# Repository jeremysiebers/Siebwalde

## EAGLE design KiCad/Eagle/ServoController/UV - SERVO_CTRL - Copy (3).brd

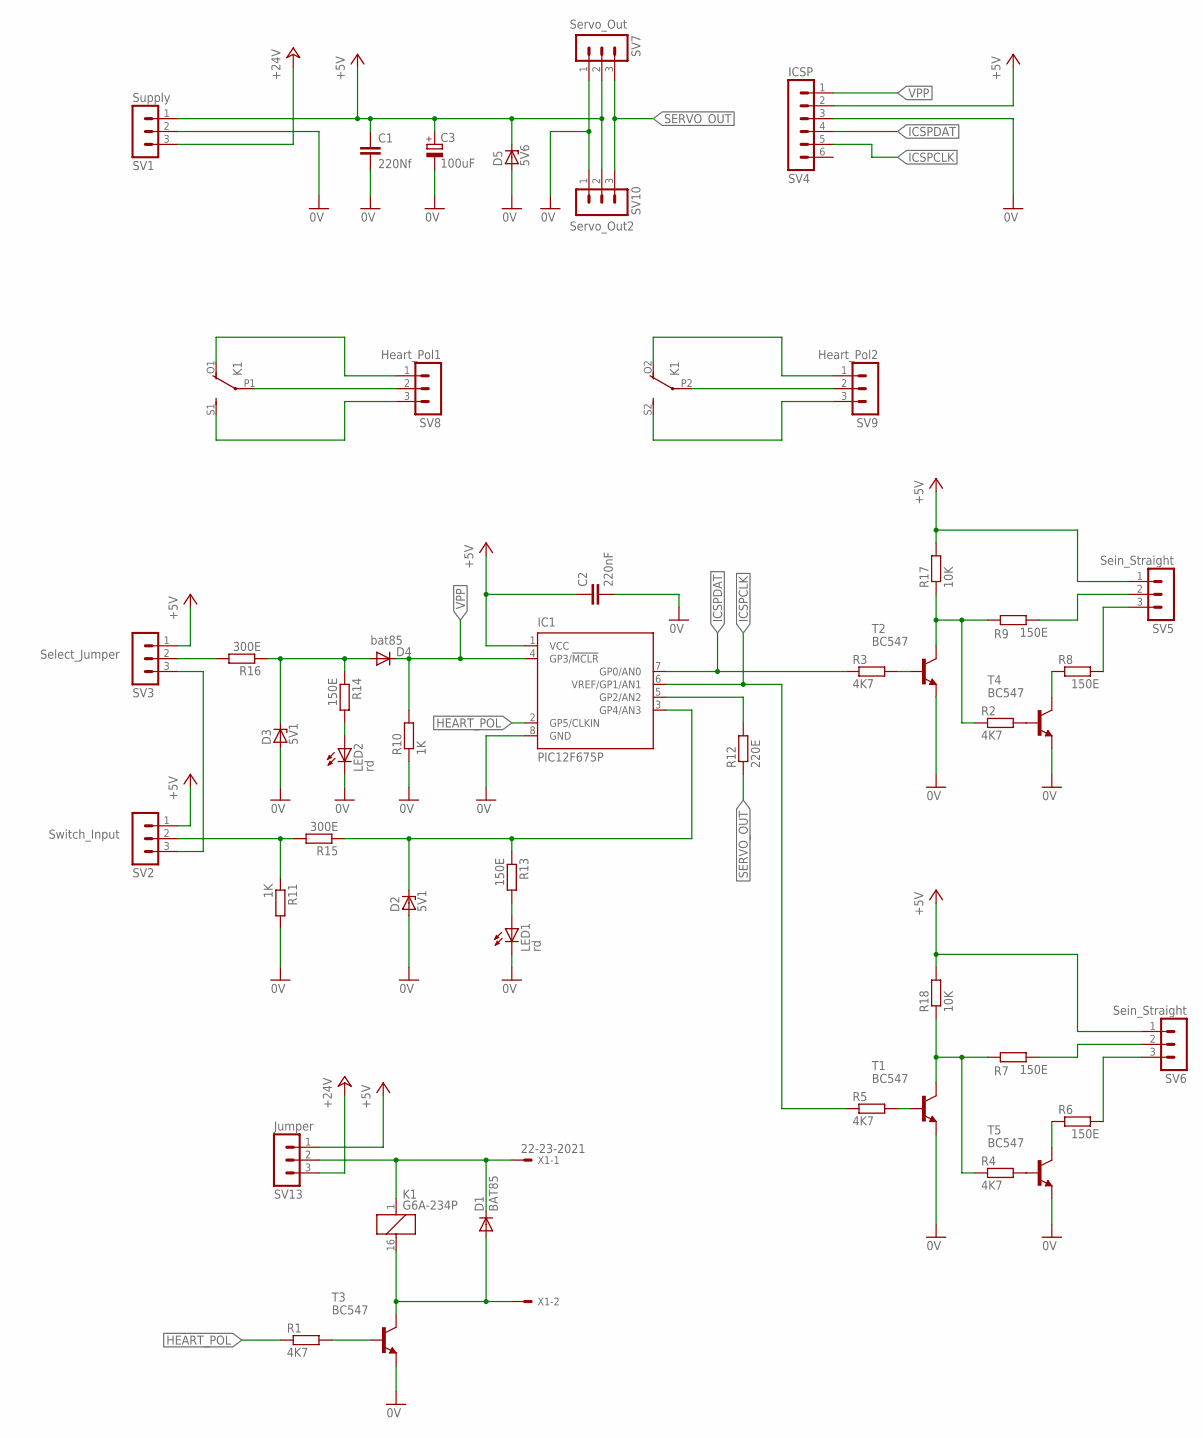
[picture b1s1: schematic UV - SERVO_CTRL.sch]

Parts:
C1: 220Nf; C050-025X075; MPN MCPBSFC-1J222KA45
C2: 220nF; C050-025X075; MPN MCPBSFC-1J222KA45
C3: 100uF; E2,5-7; MPN 107CKE035M
D1: BAT85; DO34-7; MPN BAT85,113
D2, D3: 5V1; DO34Z7; MPN BZX55C5V1-TAP
D4: bat85; DO34-7; MPN BAT85,113
D5: 5V6; C1702-15; MPN BZX85C5V1
IC1: PIC12F675P; DIL8; MPN PIC12F675-E/P
K1: G6A-234P; MPN G6A-234P-ST40-US-DC12
LED1, LED2: rd; LED3MM; MPN L-934ND
R1, R2, R3, R4, R5: 4K7; 0207/2V; MPN MCF 0.25W 4K7
R6, R7, R8, R9, R13, R14: 150E; 0207/2V; MPN MCF 0.25W 150R
R10, R11: 1K; 0207/2V; MPN MCF 0.25W 1K
R12: 220E; 0207/2V; MPN MCF 0.25W 220R
R15, R16: 300E; 0207/2V; MPN MF25 300R
R17, R18: 10K; 0207/2V; MPN MCF 0.25W 10K
SV1: Supply; MA03-1; MPN 90120-0761
SV2: Switch_Input; MA03-1; MPN 90120-0761
SV3: Select_Jumper; MA03-1; MPN 90120-0761
SV4: ICSP; MA06-1; MPN 90120-0761
SV5, SV6: Sein_Straight; MA03-1; MPN 90120-0761
SV7: Servo_Out; MA03-1; MPN 90120-0761
SV8: Heart_Pol1; MA03-1; MPN 90120-0761
SV9: Heart_Pol2; MA03-1; MPN 90120-0761
SV10: Servo_Out2; MA03-1; MPN 90120-0761
SV13: Jumper; MA03-1; MPN 90120-0761
T1, T2, T3, T4, T5: BC547; TO92; MPN BC547B
X1: 22-23-2021; MPN 22-23-2021

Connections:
0V: C1.2, C2.2, C3.-, D2.A, D3.A, D5.A, IC1.8 (GND), LED1.K (C), LED2.K (C), R10.1, R11.2, SV1.2, SV4.3, SV7.1, SV10.1, T1.1 (E), T2.1 (E), T3.1 (E), T4.1 (E), T5.1 (E)
+24V: SV1.3, SV13.3; also elsewhere on the board
HEART_POL: IC1.2 (GP5/CLKIN), R1.1
ICSPCLK: IC1.6 (VREF/GP1/AN1), R5.1, SV4.5
ICSPDAT: IC1.7 (GP0/AN0), R3.1, SV4.4
unnamed: D2.C, IC1.3 (GP4/AN3), R13.1, R15.1
unnamed: K1.O1 (O), SV8.1
unnamed: SV2.3, SV3.3
unnamed: K1.S1 (S), SV8.3
unnamed: K1.P1, SV8.2
unnamed: K1.O2 (O), SV9.1
unnamed: K1.S2 (S), SV9.3
unnamed: K1.P2, SV9.2
unnamed: IC1.5 (GP2/AN2), R12.2
unnamed: R1.2, T3.2 (B)
unnamed: D1.C, K1.1, SV13.2, X1.1
unnamed: D1.A, K1.16 (2), T3.3 (C), X1.2
unnamed: R4.2, T5.2 (B)
unnamed: R6.1, T5.3 (C)
unnamed: R6.2, SV6.3
unnamed: R5.2, T1.2 (B)
unnamed: R11.1, R15.2, SV2.2
unnamed: R4.1, R7.1, R18.1, T1.3 (C)
unnamed: R7.2, SV6.2
unnamed: R2.2, T4.2 (B)
unnamed: R8.1, T4.3 (C)
unnamed: R8.2, SV5.3
unnamed: R9.2, SV5.2
unnamed: R2.1, R9.1, R17.1, T2.3 (C)
unnamed: R3.2, T2.2 (B)
unnamed: D3.C, D4.A, R14.1, R16.1
unnamed: R16.2, SV3.2
unnamed: LED1.A, R13.2
unnamed: LED2.A, R14.2
SERVO_OUT: R12.1, SV7.3, SV10.3
VPP: D4.C, IC1.4 (GP3/!MCLR), R10.2, SV4.1

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
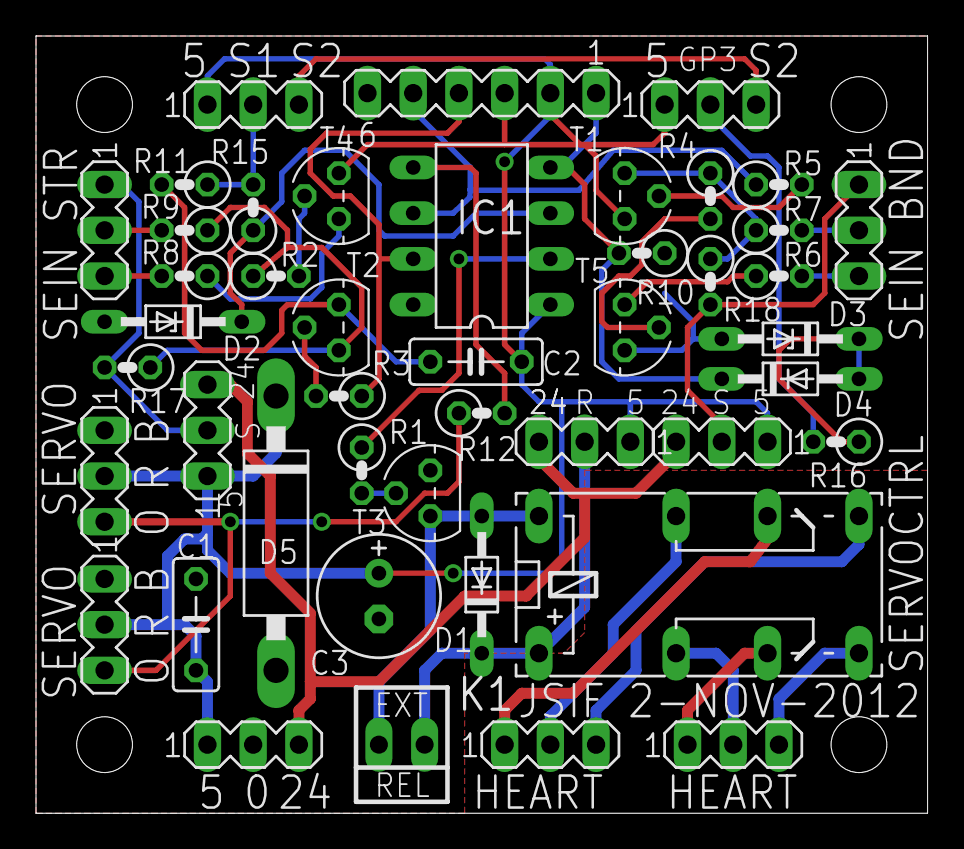
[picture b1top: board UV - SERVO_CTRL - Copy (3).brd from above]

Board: 2 copper layers, 49.5 x 43.2 mm, 45 parts (0 on the bottom side), 37 nets.

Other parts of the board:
SV11, SV12: Jumper; MA03-1

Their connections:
+24V: SV11.3, SV12.3; also elsewhere on the board
